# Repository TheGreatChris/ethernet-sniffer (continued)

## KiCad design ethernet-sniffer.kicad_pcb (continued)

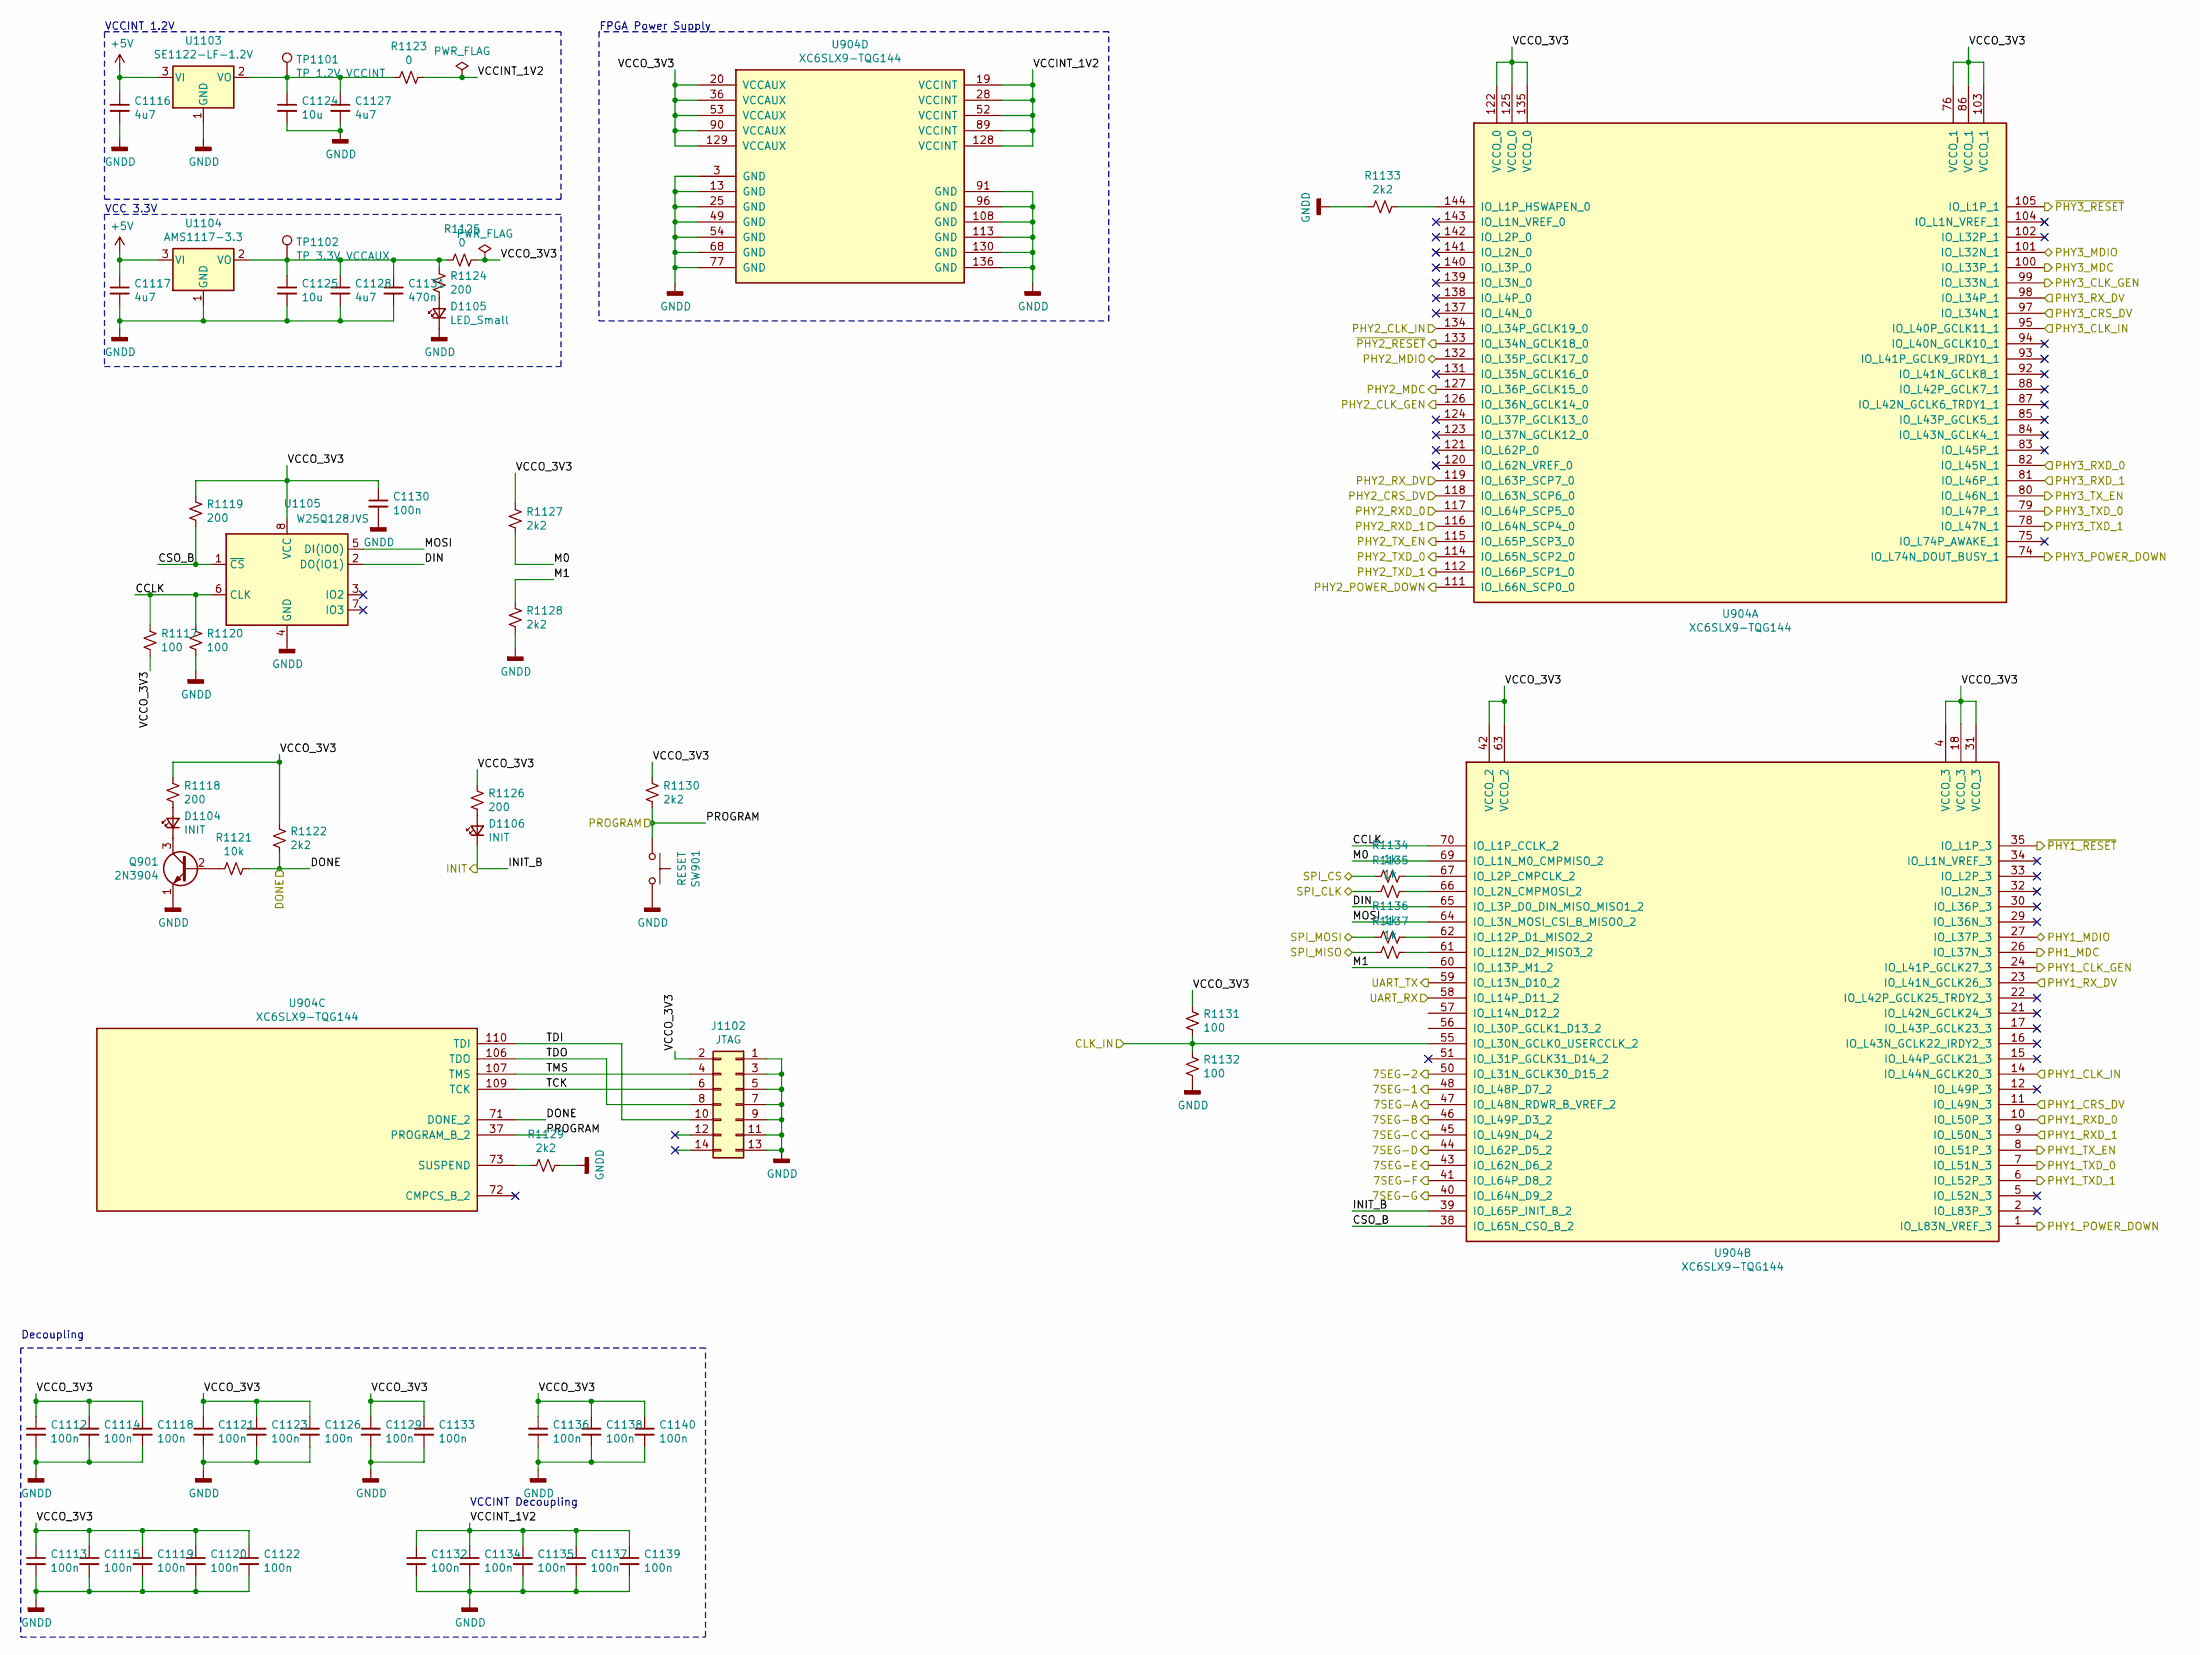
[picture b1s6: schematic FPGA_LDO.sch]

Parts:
C1112, C1113, C1114, C1115, C1118, C1119, C1120, C1121, C1122, C1123, C1126, C1129, C1130, C1132, C1133, C1134, C1135, C1136, C1137, C1138, C1139, C1140: 100n; C_0402_1005Metric
C1116, C1117, C1127, C1128: 4u7; C_0402_1005Metric
C1124, C1125: 10u; C_0402_1005Metric
C1131: 470n; C_0402_1005Metric
D1104, D1106: INIT; LED_0603_1608Metric
D1105: LED_Small; LED_0603_1608Metric
J1102: JTAG; PinHeader_2x07_P2.54mm_Vertical
Q901: 2N3904; SOT-23
R1117, R1120, R1131, R1132: 100; R_0402_1005Metric
R1118, R1119, R1124, R1126: 200; R_0402_1005Metric
R1121: 10k; R_0402_1005Metric
R1122, R1127, R1128, R1129, R1130, R1133: 2k2; R_0402_1005Metric
R1123, R1125: 0; R_0402_1005Metric
R1134, R1135, R1136, R1137: 1k; R_0402_1005Metric
SW901: RESET; SW_Push_SPST_NO_Alps_SKRK
TP1101: TP 1.2V VCCINT; TestPoint_Pad_D1.0mm
TP1102: TP 3.3V VCCAUX; TestPoint_Pad_D1.0mm
U904: XC6SLX9-TQG144; LQFP-144_20x20mm_P0.5mm
U1103: SE1122-LF-1.2V; SOT-223-3_TabPin2
U1104: AMS1117-3.3; SOT-223-3_TabPin2
U1105: W25Q128JVS; SOIC-8_5.23x5.23mm_P1.27mm

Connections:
+5V: C1116.1, C1117.1, U1103.3 (VI), U1104.3 (VI); also elsewhere on the board
/7seg-display/7SEG-1: U904.48 (IO_L48P_D7_2); also elsewhere on the board
/7seg-display/7SEG-2: U904.50 (IO_L31N_GCLK30_D15_2); also elsewhere on the board
/7seg-display/7SEG-A: U904.47 (IO_L48N_RDWR_B_VREF_2); also elsewhere on the board
/7seg-display/7SEG-B: U904.46 (IO_L49P_D3_2); also elsewhere on the board
/7seg-display/7SEG-C: U904.45 (IO_L49N_D4_2); also elsewhere on the board
/7seg-display/7SEG-D: U904.44 (IO_L62P_D5_2); also elsewhere on the board
/7seg-display/7SEG-E: U904.43 (IO_L62N_D6_2); also elsewhere on the board
/7seg-display/7SEG-F: U904.41 (IO_L64P_D8_2); also elsewhere on the board
/7seg-display/7SEG-G: U904.40 (IO_L64N_D9_2); also elsewhere on the board
/FPGA/CCLK: R1117.1, R1120.1, U904.70 (IO_L1P_CCLK_2), U1105.6 (CLK)
/FPGA/CLK_IN: R1131.2, R1132.1, U904.55 (IO_L30N_GCLK0_USERCCLK_2); also elsewhere on the board
/FPGA/CSO_B: R1119.2, U904.38 (IO_L65N_CSO_B_2), U1105.1 (~CS)
/FPGA/DIN: U904.65 (IO_L3P_D0_DIN_MISO_MISO1_2), U1105.2 (DO(IO1))
/FPGA/DONE: R1121.1, R1122.2, U904.71 (DONE_2); also elsewhere on the board
/FPGA/M0: R1127.2, U904.69 (IO_L1N_M0_CMPMISO_2)
/FPGA/M1: R1128.1, U904.60 (IO_L13P_M1_2)
/FPGA/MOSI: U904.64 (IO_L3N_MOSI_CSI_B_MISO0_2), U1105.5 (DI(IO0))
/FPGA/PHY1_POWER_DOWN: U904.1 (IO_L83N_VREF_3); also elsewhere on the board
/FPGA/PHY1_RXD_0: U904.10 (IO_L50P_3); also elsewhere on the board
/FPGA/PHY1_RXD_1: U904.9 (IO_L50N_3); also elsewhere on the board
/FPGA/PHY1_RX_DV: U904.23 (IO_L41N_GCLK26_3); also elsewhere on the board
/FPGA/PHY1_TXD_0: U904.7 (IO_L51N_3); also elsewhere on the board
/FPGA/PHY1_TXD_1: U904.6 (IO_L52P_3); also elsewhere on the board
/FPGA/PHY1_TX_EN: U904.8 (IO_L51P_3); also elsewhere on the board
/FPGA/PHY2_POWER_DOWN: U904.111 (IO_L66N_SCP0_0); also elsewhere on the board
/FPGA/PHY2_RXD_0: U904.117 (IO_L64P_SCP5_0); also elsewhere on the board
/FPGA/PHY2_RXD_1: U904.116 (IO_L64N_SCP4_0); also elsewhere on the board
/FPGA/PHY2_RX_DV: U904.119 (IO_L63P_SCP7_0); also elsewhere on the board
/FPGA/PHY2_TXD_0: U904.114 (IO_L65N_SCP2_0); also elsewhere on the board
/FPGA/PHY2_TXD_1: U904.112 (IO_L66P_SCP1_0); also elsewhere on the board
/FPGA/PHY2_TX_EN: U904.115 (IO_L65P_SCP3_0); also elsewhere on the board
/FPGA/PHY3_POWER_DOWN: U904.74 (IO_L74N_DOUT_BUSY_1); also elsewhere on the board
/FPGA/PHY3_RXD_0: U904.82 (IO_L45N_1); also elsewhere on the board
/FPGA/PHY3_RXD_1: U904.81 (IO_L46P_1); also elsewhere on the board
/FPGA/PHY3_RX_DV: U904.98 (IO_L34P_1); also elsewhere on the board
/FPGA/PHY3_TXD_0: U904.79 (IO_L47P_1); also elsewhere on the board
/FPGA/PHY3_TXD_1: U904.78 (IO_L47N_1); also elsewhere on the board
/FPGA/PHY3_TX_EN: U904.80 (IO_L46N_1); also elsewhere on the board
/FPGA/TCK: J1102.6, U904.109 (TCK)
/FPGA/TDI: J1102.10, U904.110 (TDI)
/FPGA/TDO: J1102.8, U904.106 (TDO)
/FPGA/TMS: J1102.4, U904.107 (TMS)
/FPGA/VCCINT_1V2: C1132.1, C1134.1, C1135.1, C1137.1, C1139.1, R1123.1, U904.19 (VCCINT), U904.28 (VCCINT), U904.52 (VCCINT), U904.89 (VCCINT), U904.128 (VCCINT)
/FPGA/VCCO_3V3: C1112.1, C1113.1, C1114.1, C1115.1, C1118.1, C1119.1, C1120.1, C1121.1, C1122.1, C1123.1, C1126.1, C1129.1, C1130.1, C1133.1, C1136.1, C1138.1, C1140.1, J1102.2, R1117.2, R1118.1, R1119.1, R1122.1, R1125.1, R1126.1, R1127.1, R1130.1, R1131.1, U904.4 (VCCO_3), U904.18 (VCCO_3), U904.20 (VCCAUX), U904.31 (VCCO_3), U904.36 (VCCAUX), U904.42 (VCCO_2), U904.53 (VCCAUX), U904.63 (VCCO_2), U904.76 (VCCO_1), U904.86 (VCCO_1), U904.90 (VCCAUX), U904.103 (VCCO_1), U904.122 (VCCO_0), U904.125 (VCCO_0), U904.129 (VCCAUX), U904.135 (VCCO_0), U1105.8 (VCC)
/FPGA/~PHY1_RESET: U904.35 (IO_L1P_3); also elsewhere on the board
/FPGA/~PHY2_RESET: U904.133 (IO_L34N_GCLK18_0); also elsewhere on the board
/FPGA/~PHY3_RESET: U904.105 (IO_L1P_1); also elsewhere on the board
/PHY1/CLK_OUT: U904.14 (IO_L44N_GCLK20_3); also elsewhere on the board
/PHY1/CLK_X1: U904.24 (IO_L41P_GCLK27_3); also elsewhere on the board
/PHY1/CRS_DV: U904.11 (IO_L49N_3); also elsewhere on the board
/PHY1/MDC: U904.26 (IO_L37N_3); also elsewhere on the board
/PHY1/MDIO: U904.27 (IO_L37P_3); also elsewhere on the board
/PHY2/CLK_OUT: U904.134 (IO_L34P_GCLK19_0); also elsewhere on the board
/PHY2/CLK_X1: U904.126 (IO_L36N_GCLK14_0); also elsewhere on the board
/PHY2/CRS_DV: U904.118 (IO_L63N_SCP6_0); also elsewhere on the board
/PHY2/MDC: U904.127 (IO_L36P_GCLK15_0); also elsewhere on the board
/PHY2/MDIO: U904.132 (IO_L35P_GCLK17_0); also elsewhere on the board
/PHY3/CLK_OUT: U904.95 (IO_L40P_GCLK11_1); also elsewhere on the board
/PHY3/CLK_X1: U904.99 (IO_L33N_1); also elsewhere on the board
/PHY3/CRS_DV: U904.97 (IO_L34N_1); also elsewhere on the board
/PHY3/MDC: U904.100 (IO_L33P_1); also elsewhere on the board
/PHY3/MDIO: U904.101 (IO_L32N_1); also elsewhere on the board
/STM32/FPGA_INIT: D1106.1 (K), U904.39 (IO_L65P_INIT_B_2); also elsewhere on the board
/STM32/FPGA_PROGRAM: R1130.2, SW901.1, U904.37 (PROGRAM_B_2); also elsewhere on the board
/STM32/SPI1_CS: R1134.2; also elsewhere on the board
/STM32/SPI1_MISO: R1136.2; also elsewhere on the board
/STM32/SPI1_MOSI: R1137.2; also elsewhere on the board
/STM32/SPI1_SCK: R1135.2; also elsewhere on the board
/USB-UART/UART-RX: U904.59 (IO_L13N_D10_2); also elsewhere on the board
/USB-UART/UART-TX: U904.58 (IO_L14P_D11_2); also elsewhere on the board
GNDD: C1112.2, C1113.2, C1114.2, C1115.2, C1116.2, C1117.2, C1118.2, C1119.2, C1120.2, C1121.2, C1122.2, C1123.2, C1124.2, C1125.2, C1126.2, C1127.2, C1128.2, C1129.2, C1130.2, C1131.2, C1132.2, C1133.2, C1134.2, C1135.2, C1136.2, C1137.2, C1138.2, C1139.2, C1140.2, D1105.1 (K), J1102.1, J1102.3, J1102.5, J1102.7, J1102.9, J1102.11, J1102.13, Q901.1 (E), R1120.2, R1128.2, R1129.1, R1132.2, R1133.2, SW901.2, U904.3 (GND), U904.13 (GND), U904.25 (GND), U904.49 (GND), U904.54 (GND), U904.68 (GND), U904.77 (GND), U904.91 (GND), U904.96 (GND), U904.108 (GND), U904.113 (GND), U904.130 (GND), U904.136 (GND), U1103.1 (GND), U1104.1 (GND), U1105.4 (GND); also elsewhere on the board
unnamed: C1124.1, C1127.1, R1123.2, TP1101.1, U1103.2 (VO)
unnamed: C1125.1, C1128.1, C1131.1, R1124.1, R1125.2, TP1102.1, U1104.2 (VO)
unnamed: D1104.1 (K), Q901.3 (C)
unnamed: D1104.2 (A), R1118.2
unnamed: D1105.2 (A), R1124.2
unnamed: D1106.2 (A), R1126.2
unnamed: Q901.2 (B), R1121.2
unnamed: R1129.2, U904.73 (SUSPEND)
unnamed: R1133.1, U904.144 (IO_L1P_HSWAPEN_0)
unnamed: R1134.1, U904.67 (IO_L2P_CMPCLK_2)
unnamed: R1135.1, U904.66 (IO_L2N_CMPMOSI_2)
unnamed: R1136.1, U904.62 (IO_L12P_D1_MISO2_2)
unnamed: R1137.1, U904.61 (IO_L12N_D2_MISO3_2)

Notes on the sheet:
Decoupling
VCCINT 1.2V
VCC 3.3V
VCCINT Decoupling
FPGA Power Supply

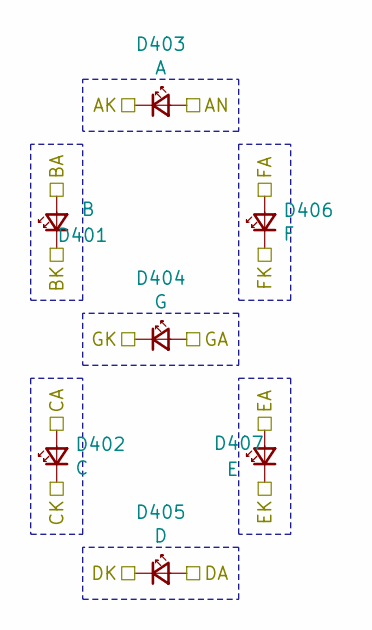
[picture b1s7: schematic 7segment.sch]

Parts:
D301: B; LED_0402_1005Metric
D302: C; LED_0402_1005Metric
D303: A; LED_0402_1005Metric
D304: G; LED_0402_1005Metric
D305: D; LED_0402_1005Metric
D306: F; LED_0402_1005Metric
D307: E; LED_0402_1005Metric

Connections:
/7seg-display/Digit 1/AK: D301.1 (K), D302.1 (K), D303.1 (K), D304.1 (K), D305.1 (K), D306.1 (K), D307.1 (K); also elsewhere on the board
/7seg-display/Digit 1/AN: D303.2 (A); also elsewhere on the board
/7seg-display/Digit 1/BA: D301.2 (A); also elsewhere on the board
/7seg-display/Digit 1/CA: D302.2 (A); also elsewhere on the board
/7seg-display/Digit 1/DA: D305.2 (A); also elsewhere on the board
/7seg-display/Digit 1/EA: D307.2 (A); also elsewhere on the board
/7seg-display/Digit 1/FA: D306.2 (A); also elsewhere on the board
/7seg-display/Digit 1/GA: D304.2 (A); also elsewhere on the board

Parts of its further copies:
D401: B; LED_0402_1005Metric
D402: C; LED_0402_1005Metric
D403: A; LED_0402_1005Metric
D404: G; LED_0402_1005Metric
D405: D; LED_0402_1005Metric
D406: F; LED_0402_1005Metric
D407: E; LED_0402_1005Metric

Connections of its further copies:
/7seg-display/Digit 1/AN: D403.2 (A); also elsewhere on the board
/7seg-display/Digit 1/BA: D401.2 (A); also elsewhere on the board
/7seg-display/Digit 1/CA: D402.2 (A); also elsewhere on the board
/7seg-display/Digit 1/DA: D405.2 (A); also elsewhere on the board
/7seg-display/Digit 1/EA: D407.2 (A); also elsewhere on the board
/7seg-display/Digit 1/FA: D406.2 (A); also elsewhere on the board
/7seg-display/Digit 1/GA: D404.2 (A); also elsewhere on the board
/7seg-display/Digit 2/AK: D401.1 (K), D402.1 (K), D403.1 (K), D404.1 (K), D405.1 (K), D406.1 (K), D407.1 (K); also elsewhere on the board

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
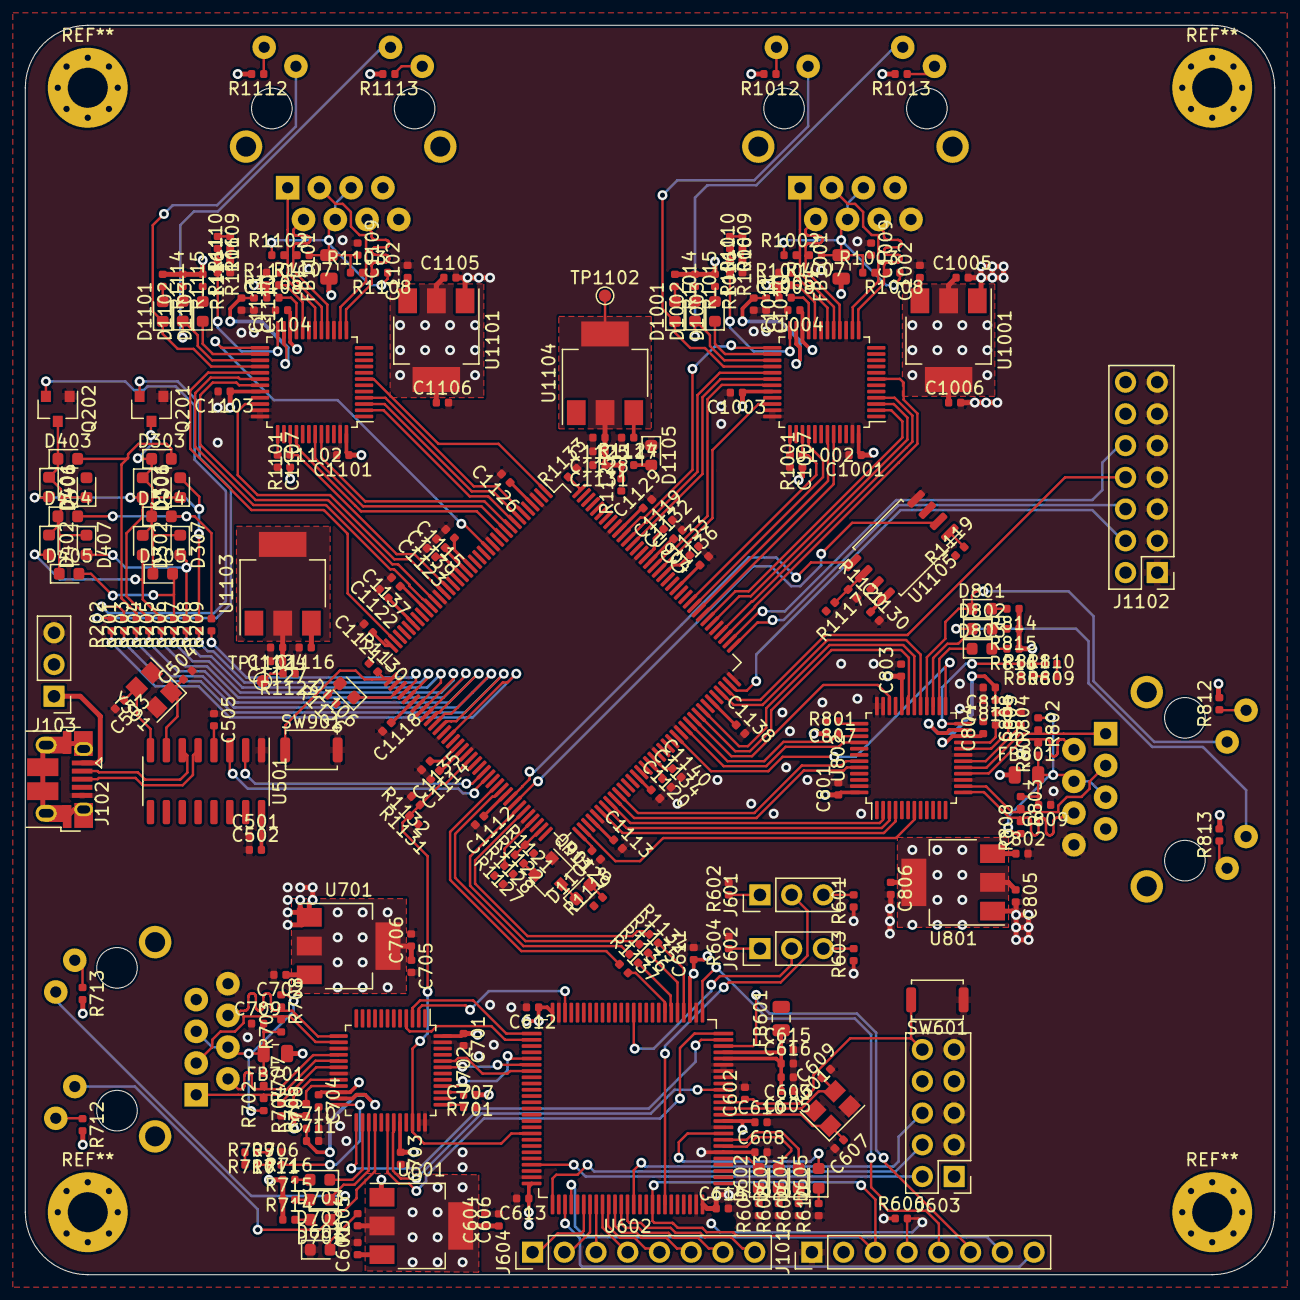
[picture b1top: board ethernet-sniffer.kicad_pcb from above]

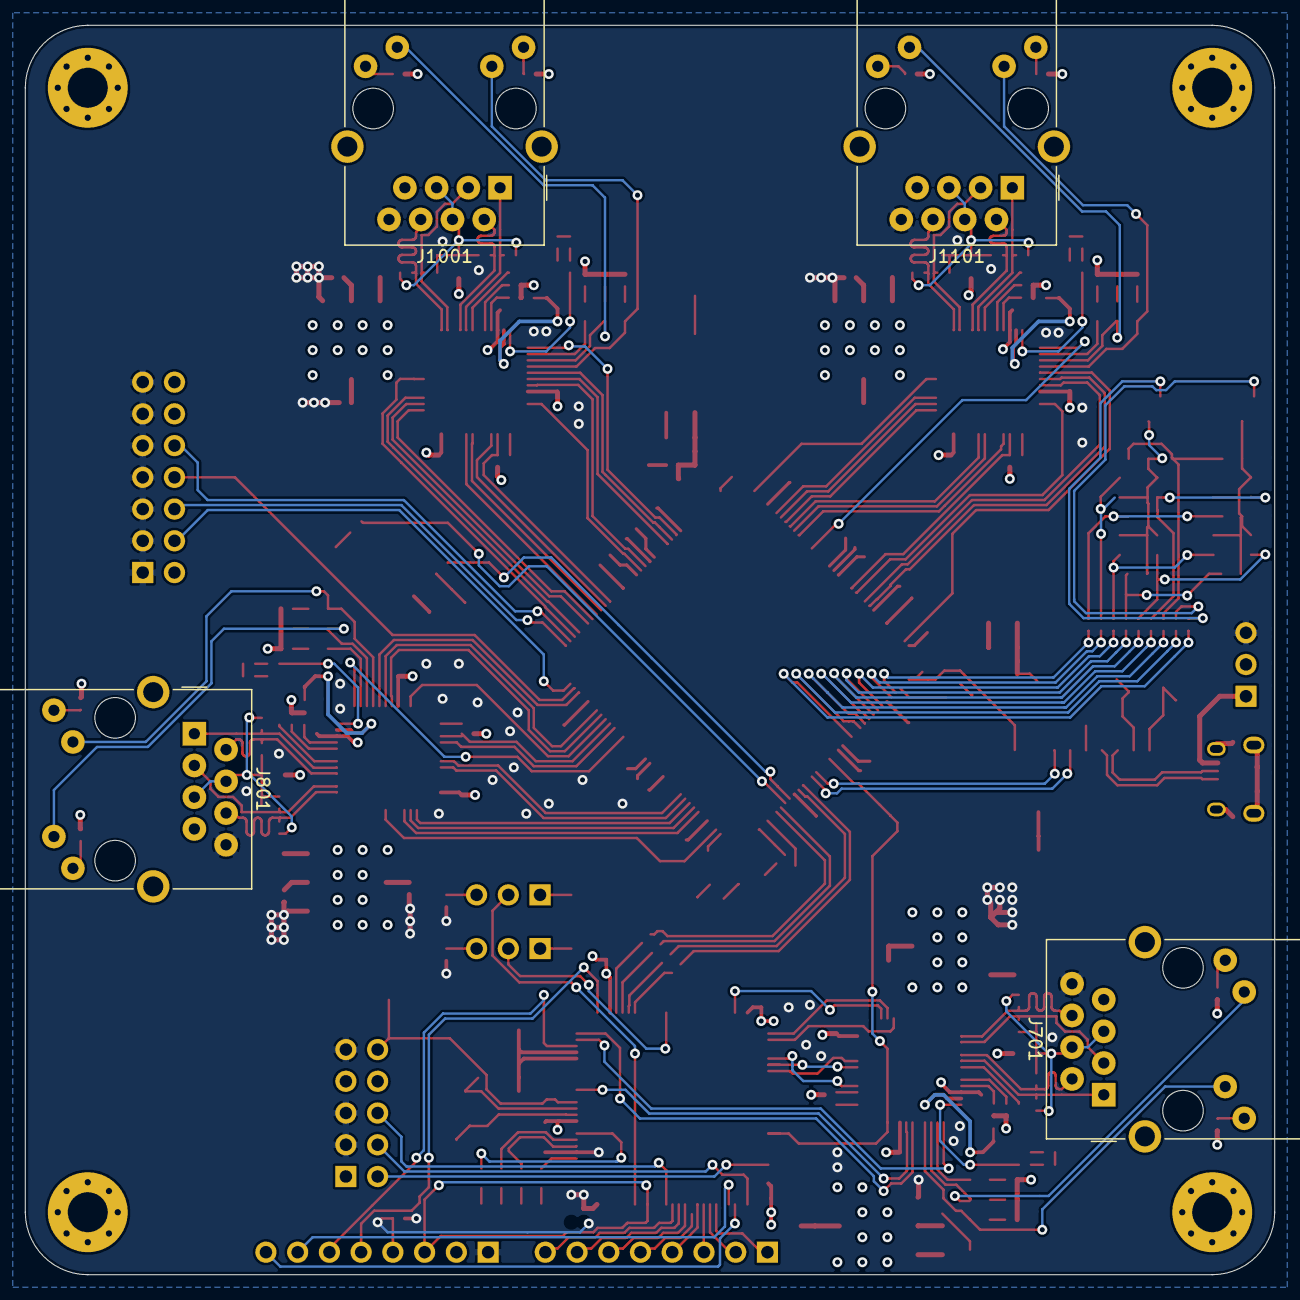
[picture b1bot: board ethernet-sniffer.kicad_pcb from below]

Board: 4 copper layers, 100.0 x 100.0 mm, 273 parts (4 on the bottom side), 241 nets.

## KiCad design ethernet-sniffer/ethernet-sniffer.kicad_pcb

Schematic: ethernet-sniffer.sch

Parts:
J101: Conn_01x06; PinHeader_1x06_P2.54mm_Vertical
J102: USB_B_Micro; USB_Micro-B_Amphenol_10103594-0001LF_Horizontal
J103: POWER 5V; PinHeader_1x03_P2.54mm_Vertical

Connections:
+5V: J103.2; also elsewhere on the board
/STM32/ADC1: J101.3; also elsewhere on the board
/STM32/ADC2: J101.4; also elsewhere on the board
/STM32/I2C_SCL: J101.6; also elsewhere on the board
/STM32/I2C_SDA: J101.5; also elsewhere on the board
/STM32/UART_RX: J101.2; also elsewhere on the board
/STM32/UART_TX: J101.1; also elsewhere on the board
/USB-UART/USB-D+: J102.3 (D+); also elsewhere on the board
/USB-UART/USB-D-: J102.2 (D-); also elsewhere on the board
GNDD: J102.5 (GND), J103.3; also elsewhere on the board
unnamed: J102.1 (VBUS), J103.1

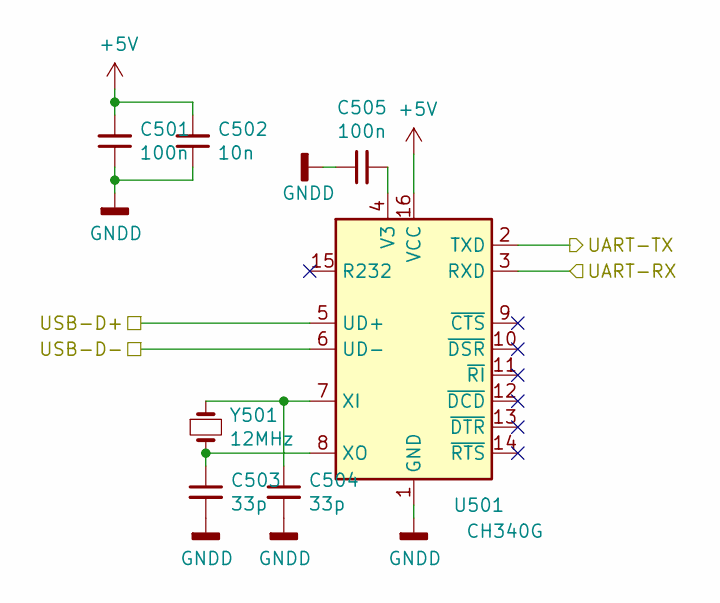
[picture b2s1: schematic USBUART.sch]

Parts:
C501, C505: 100n; C_0402_1005Metric
C502: 10n; C_0402_1005Metric
C503, C504: 33p; C_0402_1005Metric
U501: CH340G; SOIC-16_3.9x9.9mm_P1.27mm
Y501: 12MHz; Crystal_SMD_0603-2Pin_6.0x3.5mm

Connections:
+5V: C501.2, C502.2, U501.16 (VCC); also elsewhere on the board
/USB-UART/UART-RX: U501.3 (RXD); also elsewhere on the board
/USB-UART/UART-TX: U501.2 (TXD); also elsewhere on the board
/USB-UART/USB-D+: U501.5 (UD+); also elsewhere on the board
/USB-UART/USB-D-: U501.6 (UD-); also elsewhere on the board
GNDD: C501.1, C502.1, C503.2, C504.2, C505.1, U501.1 (GND); also elsewhere on the board
unnamed: C503.1, U501.8 (XO), Y501.2
unnamed: C504.1, U501.7 (XI), Y501.1
unnamed: C505.2, U501.4 (V3)

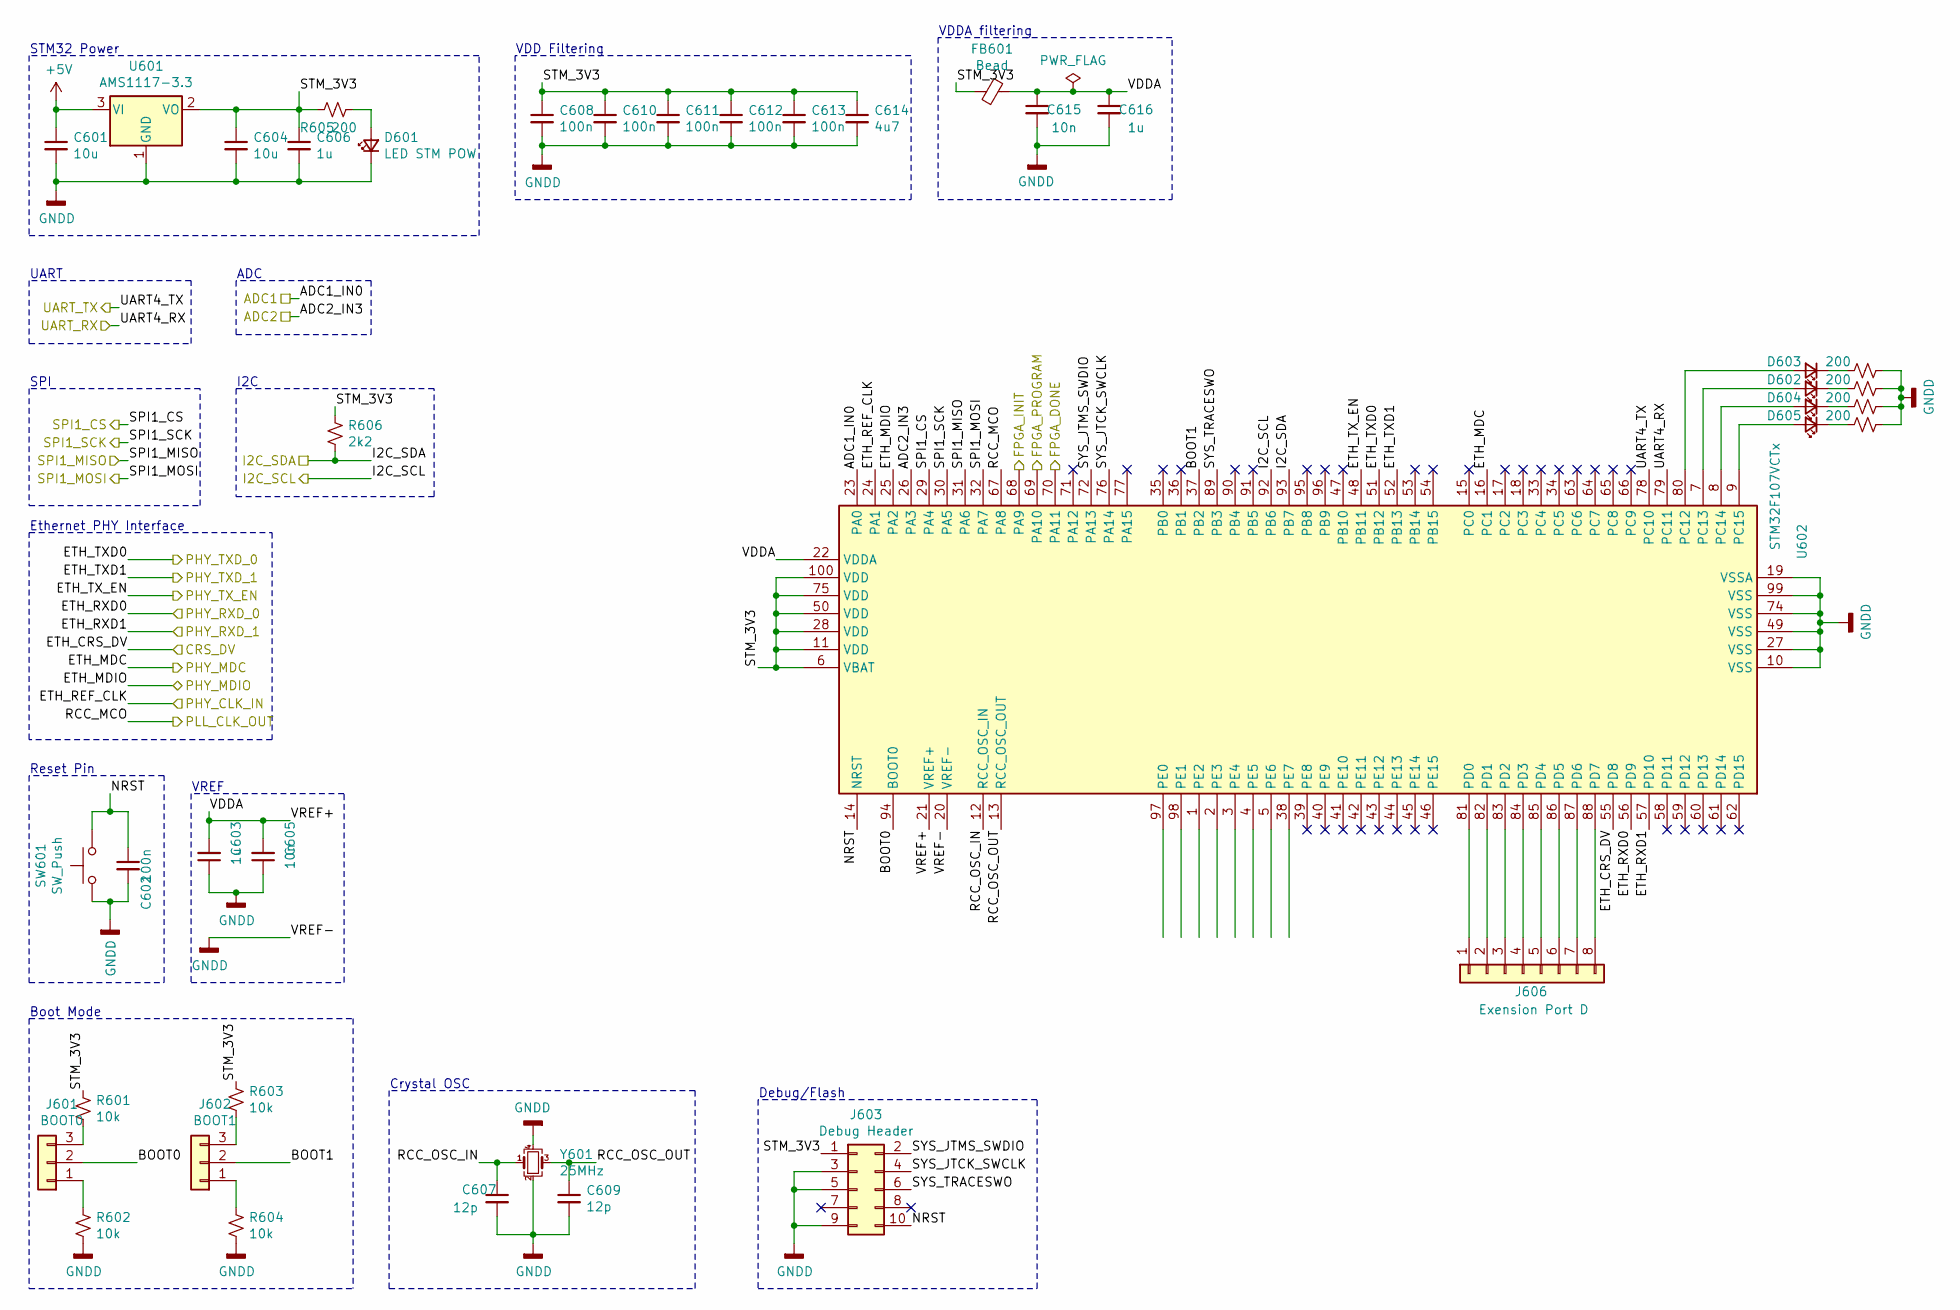
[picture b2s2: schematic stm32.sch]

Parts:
C601, C604: 10u; C_0402_1005Metric
C602, C608, C610, C611, C612, C613: 100n; C_0402_1005Metric
C603, C606, C616: 1u; C_0402_1005Metric
C605, C615: 10n; C_0402_1005Metric
C607, C609: 12p; C_0402_1005Metric
C614: 4u7; C_0402_1005Metric
D601: LED STM POW; LED_0603_1608Metric
D602, D603, D604, D605: LED_Small; LED_0603_1608Metric
FB601: Bead; L_0805_2012Metric
J601: BOOT0; PinHeader_1x03_P2.54mm_Vertical
J602: BOOT1; PinHeader_1x03_P2.54mm_Vertical
J603: Debug Header; PinHeader_2x05_P2.54mm_Vertical
J606: Exension Port D; PinHeader_1x08_P2.54mm_Vertical
R601, R602, R603, R604: 10k; R_0402_1005Metric
R605, R607, R608, R609, R610: 200; R_0402_1005Metric
R606: 2k2; R_0402_1005Metric
SW601: SW_Push; SW_Push_SPST_NO_Alps_SKRK
U601: AMS1117-3.3; SOT-223-3_TabPin2
U602: STM32F107VCTx; LQFP-100_14x14mm_P0.5mm
Y601: 25MHz; Crystal_SMD_5032-4Pin_5.0x3.2mm

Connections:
+5V: C601.1, U601.3 (VI); also elsewhere on the board
/100BASETX-PHY 1/CLK_OUT: U602.24 (PA1); also elsewhere on the board
/100BASETX-PHY 1/CRS_DV: U602.55 (PD8); also elsewhere on the board
/100BASETX-PHY 1/MDC: U602.16 (PC1); also elsewhere on the board
/100BASETX-PHY 1/MDIO: U602.25 (PA2); also elsewhere on the board
/FPGA/CLK_IN: U602.67 (PA8); also elsewhere on the board
/FPGA/DONE: U602.70 (PA11); also elsewhere on the board
/STM32/ADC1: U602.23 (PA0); also elsewhere on the board
/STM32/ADC2: U602.26 (PA3); also elsewhere on the board
/STM32/BOOT0: J601.2, U602.94 (BOOT0)
/STM32/BOOT1: J602.2, U602.37 (PB2)
/STM32/FPGA_INIT: U602.68 (PA9); also elsewhere on the board
/STM32/FPGA_PROGRAM: U602.69 (PA10); also elsewhere on the board
/STM32/I2C_SCL: U602.92 (PB6); also elsewhere on the board
/STM32/I2C_SDA: R606.2, U602.93 (PB7); also elsewhere on the board
/STM32/NRST: C602.1, J603.10, SW601.2, U602.14 (NRST)
/STM32/PHY_RXD_0: U602.56 (PD9); also elsewhere on the board
/STM32/PHY_RXD_1: U602.57 (PD10); also elsewhere on the board
/STM32/PHY_TXD_0: U602.51 (PB12); also elsewhere on the board
/STM32/PHY_TXD_1: U602.52 (PB13); also elsewhere on the board
/STM32/PHY_TX_EN: U602.48 (PB11); also elsewhere on the board
/STM32/RCC_OSC_IN: C607.1, U602.12 (RCC_OSC_IN), Y601.1
/STM32/RCC_OSC_OUT: C609.1, U602.13 (RCC_OSC_OUT), Y601.3
/STM32/SPI1_CS: U602.29 (PA4); also elsewhere on the board
/STM32/SPI1_MISO: U602.31 (PA6); also elsewhere on the board
/STM32/SPI1_MOSI: U602.32 (PA7); also elsewhere on the board
/STM32/SPI1_SCK: U602.30 (PA5); also elsewhere on the board
/STM32/STM_3V3: C604.1, C606.1, C608.1, C610.1, C611.1, C612.1, C613.1, C614.1, FB601.2, J603.1, R601.1, R603.1, R605.1, R606.1, U601.2 (VO), U602.6 (VBAT), U602.11 (VDD), U602.28 (VDD), U602.50 (VDD), U602.75 (VDD), U602.100 (VDD)
/STM32/SYS_JTCK_SWCLK: J603.4, U602.76 (PA14)
/STM32/SYS_JTMS_SWDIO: J603.2, U602.72 (PA13)
/STM32/SYS_TRACESWO: J603.6, U602.89 (PB3)
/STM32/UART_RX: U602.79 (PC11); also elsewhere on the board
/STM32/UART_TX: U602.78 (PC10); also elsewhere on the board
/STM32/VDDA: C603.2, C605.2, C615.1, C616.1, FB601.1, U602.21 (VREF+), U602.22 (VDDA)
GNDD: C601.2, C602.2, C603.1, C604.2, C605.1, C606.2, C607.2, C608.2, C609.2, C610.2, C611.2, C612.2, C613.2, C614.2, C615.2, C616.2, D601.1 (K), J603.3, J603.5, J603.9, R602.2, R604.2, R607.1, R608.1, R609.1, R610.1, SW601.1, U601.1 (GND), U602.10 (VSS), U602.19 (VSSA), U602.20 (VREF-), U602.27 (VSS), U602.49 (VSS), U602.74 (VSS), U602.99 (VSS), Y601.2, Y601.4; also elsewhere on the board
unnamed: D601.2 (A), R605.2
unnamed: D602.1 (K), R607.2
unnamed: D602.2 (A), U602.80 (PC12)
unnamed: D603.1 (K), R608.2
unnamed: D603.2 (A), U602.7 (PC13)
unnamed: D604.1 (K), R609.2
unnamed: D604.2 (A), U602.8 (PC14)
unnamed: D605.1 (K), R610.2
unnamed: D605.2 (A), U602.9 (PC15)
unnamed: J601.1, R602.1
unnamed: J601.3, R601.2
unnamed: J602.1, R604.1
unnamed: J602.3, R603.2
unnamed: J606.1, U602.81 (PD0)
unnamed: J606.2, U602.82 (PD1)
unnamed: J606.3, U602.83 (PD2)
unnamed: J606.4, U602.84 (PD3)
unnamed: J606.5, U602.85 (PD4)
unnamed: J606.6, U602.86 (PD5)
unnamed: J606.7, U602.87 (PD6)
unnamed: J606.8, U602.88 (PD7)

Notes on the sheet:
Reset Pin
Boot Mode
VREF
Crystal OSC
Debug/Flash
Ethernet PHY Interface
SPI
STM32 Power
VDD Filtering
UART
ADC
VDDA filtering
I2C
